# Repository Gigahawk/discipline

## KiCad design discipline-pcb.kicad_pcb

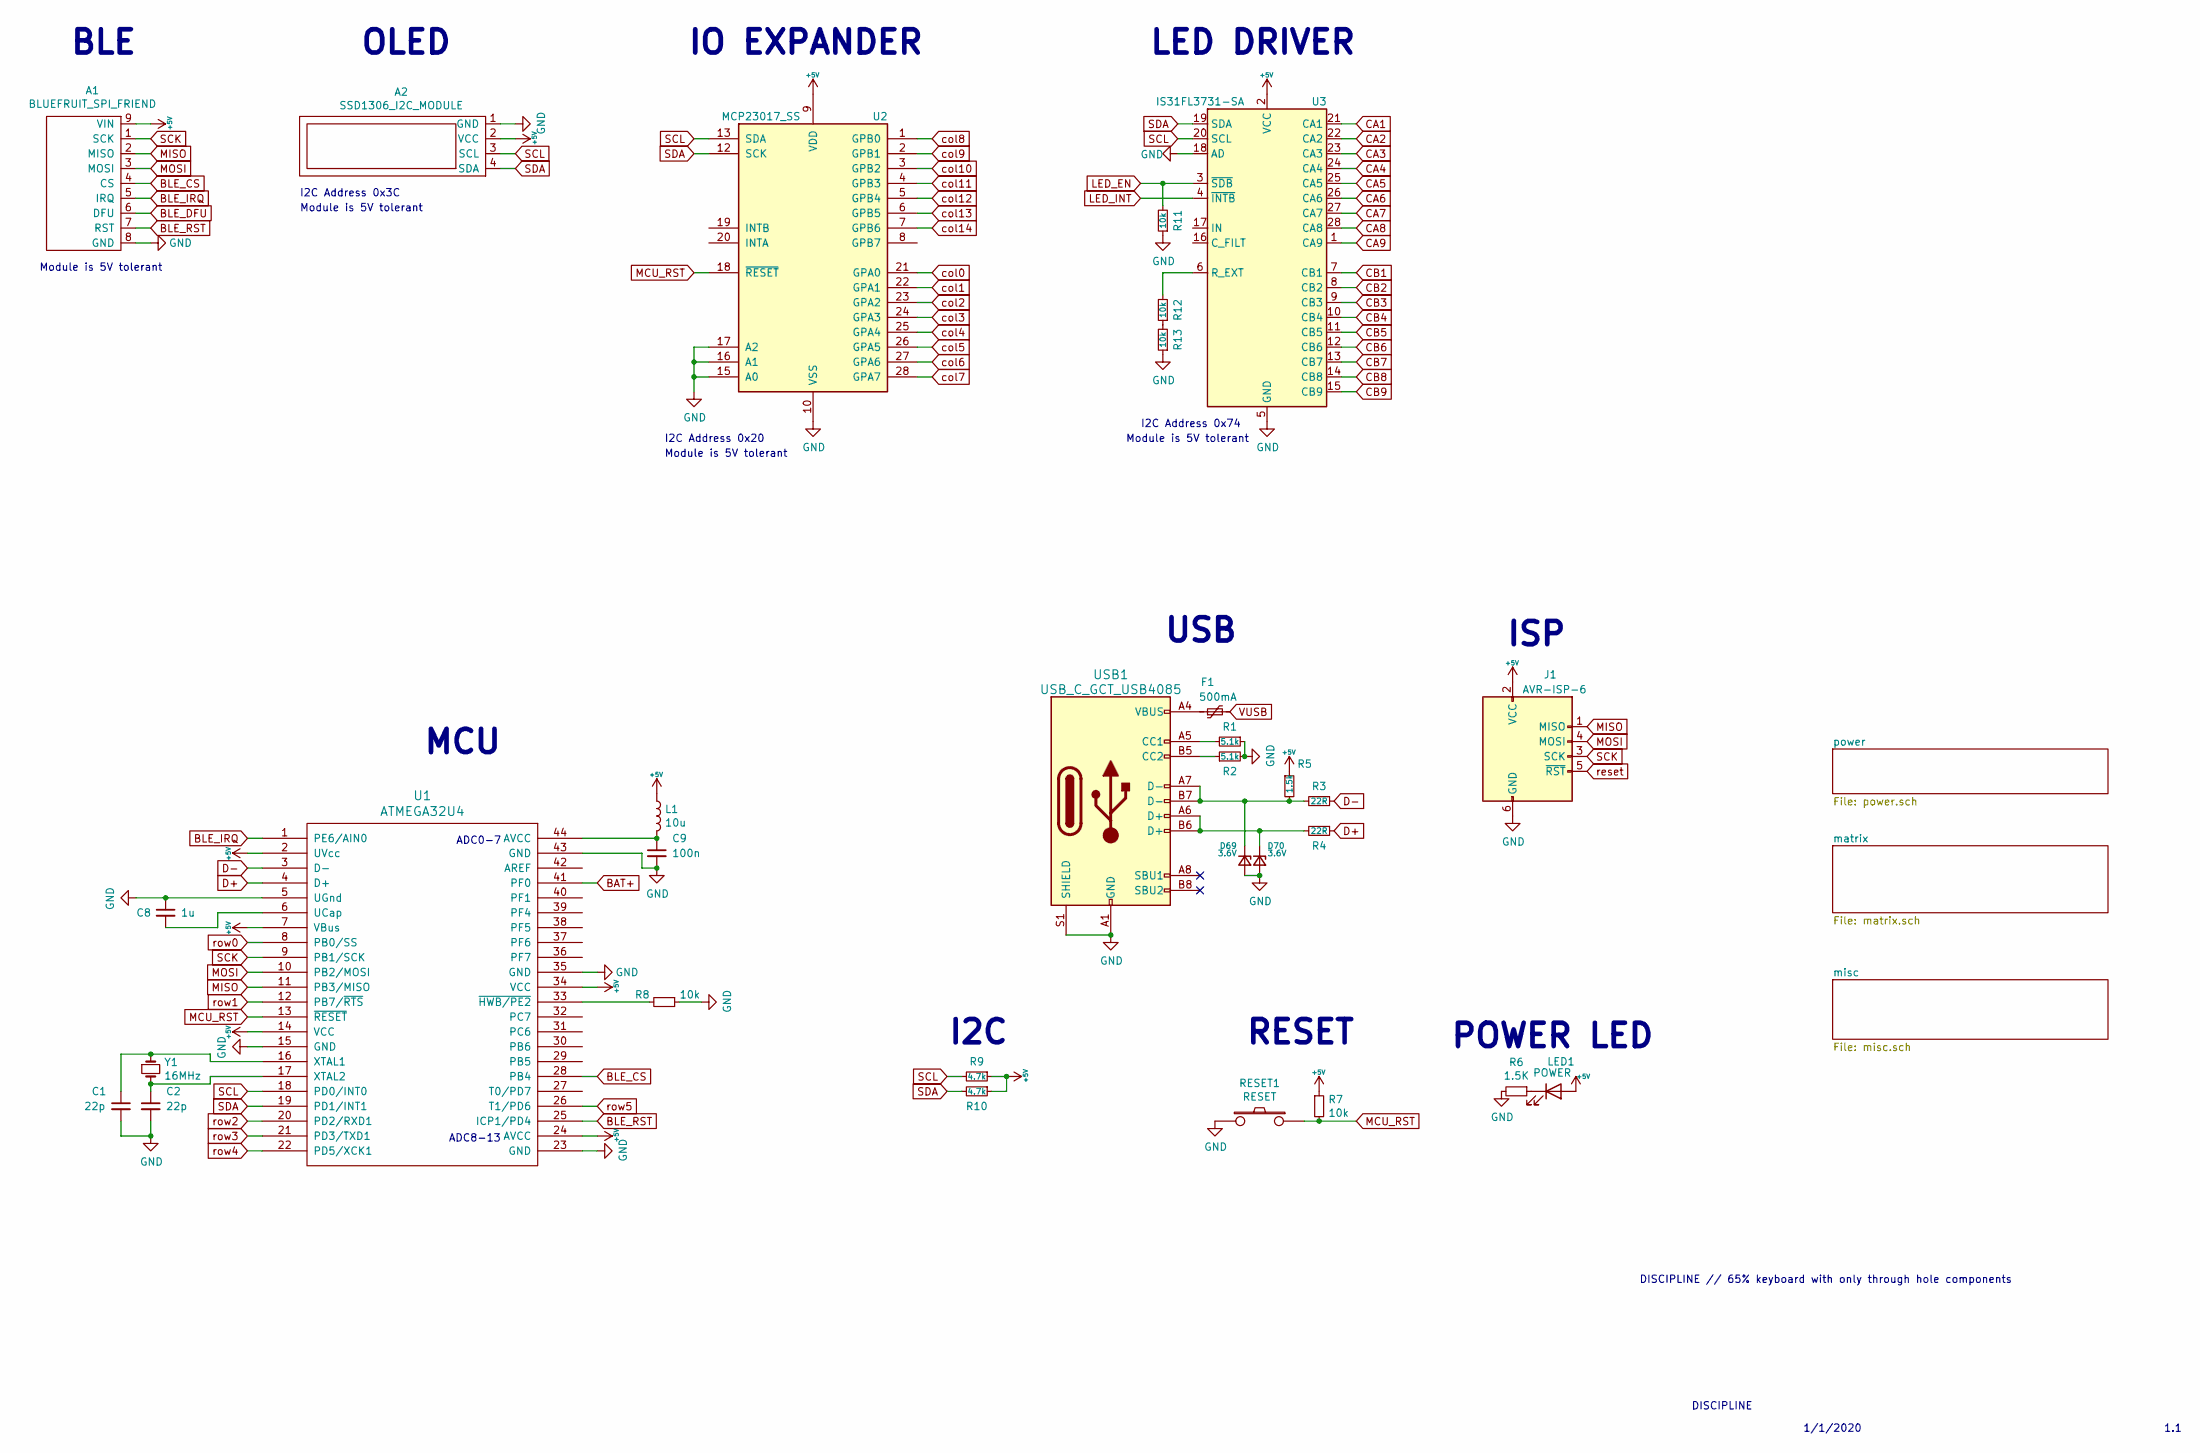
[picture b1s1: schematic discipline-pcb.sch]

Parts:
A1: BLUEFRUIT_SPI_FRIEND
A2: SSD1306_I2C_MODULE; SSD1306_MODULE_128x32
C1, C2: 22p; C_Disc_D3.0mm_W1.6mm_P2.50mm
C8: 1u; C_Disc_D3.0mm_W1.6mm_P2.50mm
C9: 100n; C_Disc_D3.0mm_W1.6mm_P2.50mm
D69, D70: 3.6V; D_SOD123_axial
F1: 500mA; polyfuse_5.1mm
J1: AVR-ISP-6; AVR_ICSP_3x2
L1: 10u
LED1: POWER; LED_D3.0mm
R1, R2: 5.1k; R_Axial_DIN0204_L3.6mm_D1.6mm_P5.08mm_Horizontal
R3, R4: 22R; R_Axial_DIN0204_L3.6mm_D1.6mm_P5.08mm_Horizontal
R5: 1.5k; R_Axial_DIN0204_L3.6mm_D1.6mm_P5.08mm_Horizontal
R6: 1.5K; R_Axial_DIN0204_L3.6mm_D1.6mm_P5.08mm_Horizontal
R7, R8, R11, R12, R13: 10k; R_Axial_DIN0204_L3.6mm_D1.6mm_P5.08mm_Horizontal
R9, R10: 4.7k; R_Axial_DIN0204_L3.6mm_D1.6mm_P5.08mm_Horizontal
RESET1: RESET; SW_PUSH_6mm
U1: ATMEGA32U4; TQFP-44_10x10mm_P0.8mm
U2: MCP23017_SS; SSOP-28_5.3x10.2mm_P0.65mm
U3: IS31FL3731-SA; SSOP-28_5.3x10.2mm_P0.65mm
USB1: USB_C_GCT_USB4085
Y1: 16MHz; Crystal_HC49-4H_Vertical

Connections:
+5V: A1.9 (VIN), A2.2 (VCC), J1.2 (VCC), L1.1, LED1.2 (A), R5.1, R7.1, R9.1, R10.1, U1.2 (UVcc), U1.7 (VBus), U1.14 (VCC), U1.24 (AVCC), U1.34 (VCC), U2.9 (VDD), U3.2 (VCC); also elsewhere on the board
BAT+: U1.41 (PF0); also elsewhere on the board
BLE_CS: A1.4 (CS), U1.28 (PB4)
BLE_DFU: A1.6 (DFU)
BLE_IRQ: A1.5 (IRQ), U1.1 (PE6/AIN0)
BLE_RST: A1.7 (RST), U1.25 (ICP1/PD4)
CA1: U3.21 (CA1); also elsewhere on the board
CA2: U3.22 (CA2); also elsewhere on the board
CA3: U3.23 (CA3); also elsewhere on the board
CA4: U3.24 (CA4); also elsewhere on the board
CA5: U3.25 (CA5); also elsewhere on the board
CA6: U3.26 (CA6); also elsewhere on the board
CA7: U3.27 (CA7); also elsewhere on the board
CA8: U3.28 (CA8); also elsewhere on the board
CA9: U3.1 (CA9); also elsewhere on the board
CB1: U3.7 (CB1); also elsewhere on the board
CB2: U3.8 (CB2); also elsewhere on the board
CB3: U3.9 (CB3); also elsewhere on the board
CB4: U3.10 (CB4); also elsewhere on the board
CB5: U3.11 (CB5); also elsewhere on the board
CB6: U3.12 (CB6); also elsewhere on the board
CB7: U3.13 (CB7); also elsewhere on the board
CB8: U3.14 (CB8); also elsewhere on the board
CB9: U3.15 (CB9)
D+: R4.1, U1.4 (D+)
D-: R3.1, U1.3 (D-)
GND: A1.8 (GND), A2.1 (GND), C1.2, C2.2, C8.1, C9.2, D69.2 (A), D70.2 (A), J1.6 (GND), R1.1, R2.2, R6.2, R8.1, R11.1, R13.1, RESET1.2, U1.5 (UGnd), U1.15 (GND), U1.23 (GND), U1.35 (GND), U1.43 (GND), U2.10 (VSS), U2.15 (A0), U2.16 (A1), U2.17 (A2), U3.5 (GND), U3.18 (AD), USB1.A1 (GND), USB1.A12 (GND), USB1.B1 (GND), USB1.B12 (GND), USB1.S1 (SHIELD); also elsewhere on the board
LED_EN: R11.2, U3.3 (~SDB)
LED_INT: U3.4 (~INTB)
MCU_RST: R7.2, RESET1.1, U1.13 (~RESET), U2.18 (~RESET~)
MISO: A1.2 (MISO), J1.1 (MISO), U1.11 (PB3/MISO)
MOSI: A1.3 (MOSI), J1.4 (MOSI), U1.10 (PB2/MOSI)
unnamed: C1.1, U1.16 (XTAL1), Y1.1
unnamed: C2.1, U1.17 (XTAL2), Y1.2
unnamed: C8.2, U1.6 (UCap)
unnamed: C9.1, L1.2, U1.44 (AVCC)
unnamed: D69.1 (K), R3.2, R5.2, USB1.A7 (D-), USB1.B7 (D-)
unnamed: D70.1 (K), R4.2, USB1.A6 (D+), USB1.B6 (D+)
unnamed: F1.1, USB1.A4 (VBUS), USB1.A9 (VBUS), USB1.B4 (VBUS), USB1.B9 (VBUS)
unnamed: LED1.1 (K), R6.1
unnamed: R1.2, USB1.A5 (CC1)
unnamed: R2.1, USB1.B5 (CC2)
unnamed: R8.2, U1.33 (~HWB/PE2)
unnamed: R12.1, R13.2
unnamed: R12.2, U3.6 (R_EXT)
SCK: A1.1 (SCK), J1.3 (SCK), U1.9 (PB1/SCK)
SCL: A2.3 (SCL), R9.2, U1.18 (PD0/INT0), U2.13 (SDA), U3.20 (SCL)
SDA: A2.4 (SDA), R10.2, U1.19 (PD1/INT1), U2.12 (SCK), U3.19 (SDA)
VUSB: F1.2; also elsewhere on the board
col0: U2.21 (GPA0); also elsewhere on the board
col1: U2.22 (GPA1); also elsewhere on the board
col2: U2.23 (GPA2); also elsewhere on the board
col3: U2.24 (GPA3); also elsewhere on the board
col4: U2.25 (GPA4); also elsewhere on the board
col5: U2.26 (GPA5); also elsewhere on the board
col6: U2.27 (GPA6); also elsewhere on the board
col7: U2.28 (GPA7); also elsewhere on the board
col8: U2.1 (GPB0); also elsewhere on the board
col9: U2.2 (GPB1); also elsewhere on the board
col10: U2.3 (GPB2); also elsewhere on the board
col11: U2.4 (GPB3); also elsewhere on the board
col12: U2.5 (GPB4); also elsewhere on the board
col13: U2.6 (GPB5); also elsewhere on the board
col14: U2.7 (GPB6); also elsewhere on the board
reset: J1.5 (~RST)

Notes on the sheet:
DISCIPLINE // 65% keyboard with only through hole components
1/1/2020
DISCIPLINE
1.1
MCU
USB
ISP
RESET
POWER LED
BLE
OLED
Module is 5V tolerant
Module is 5V tolerant
I2C Address 0x3C
ADC0-7
ADC8-13
IO EXPANDER
I2C Address 0x20
LED DRIVER
I2C Address 0x74
I2C

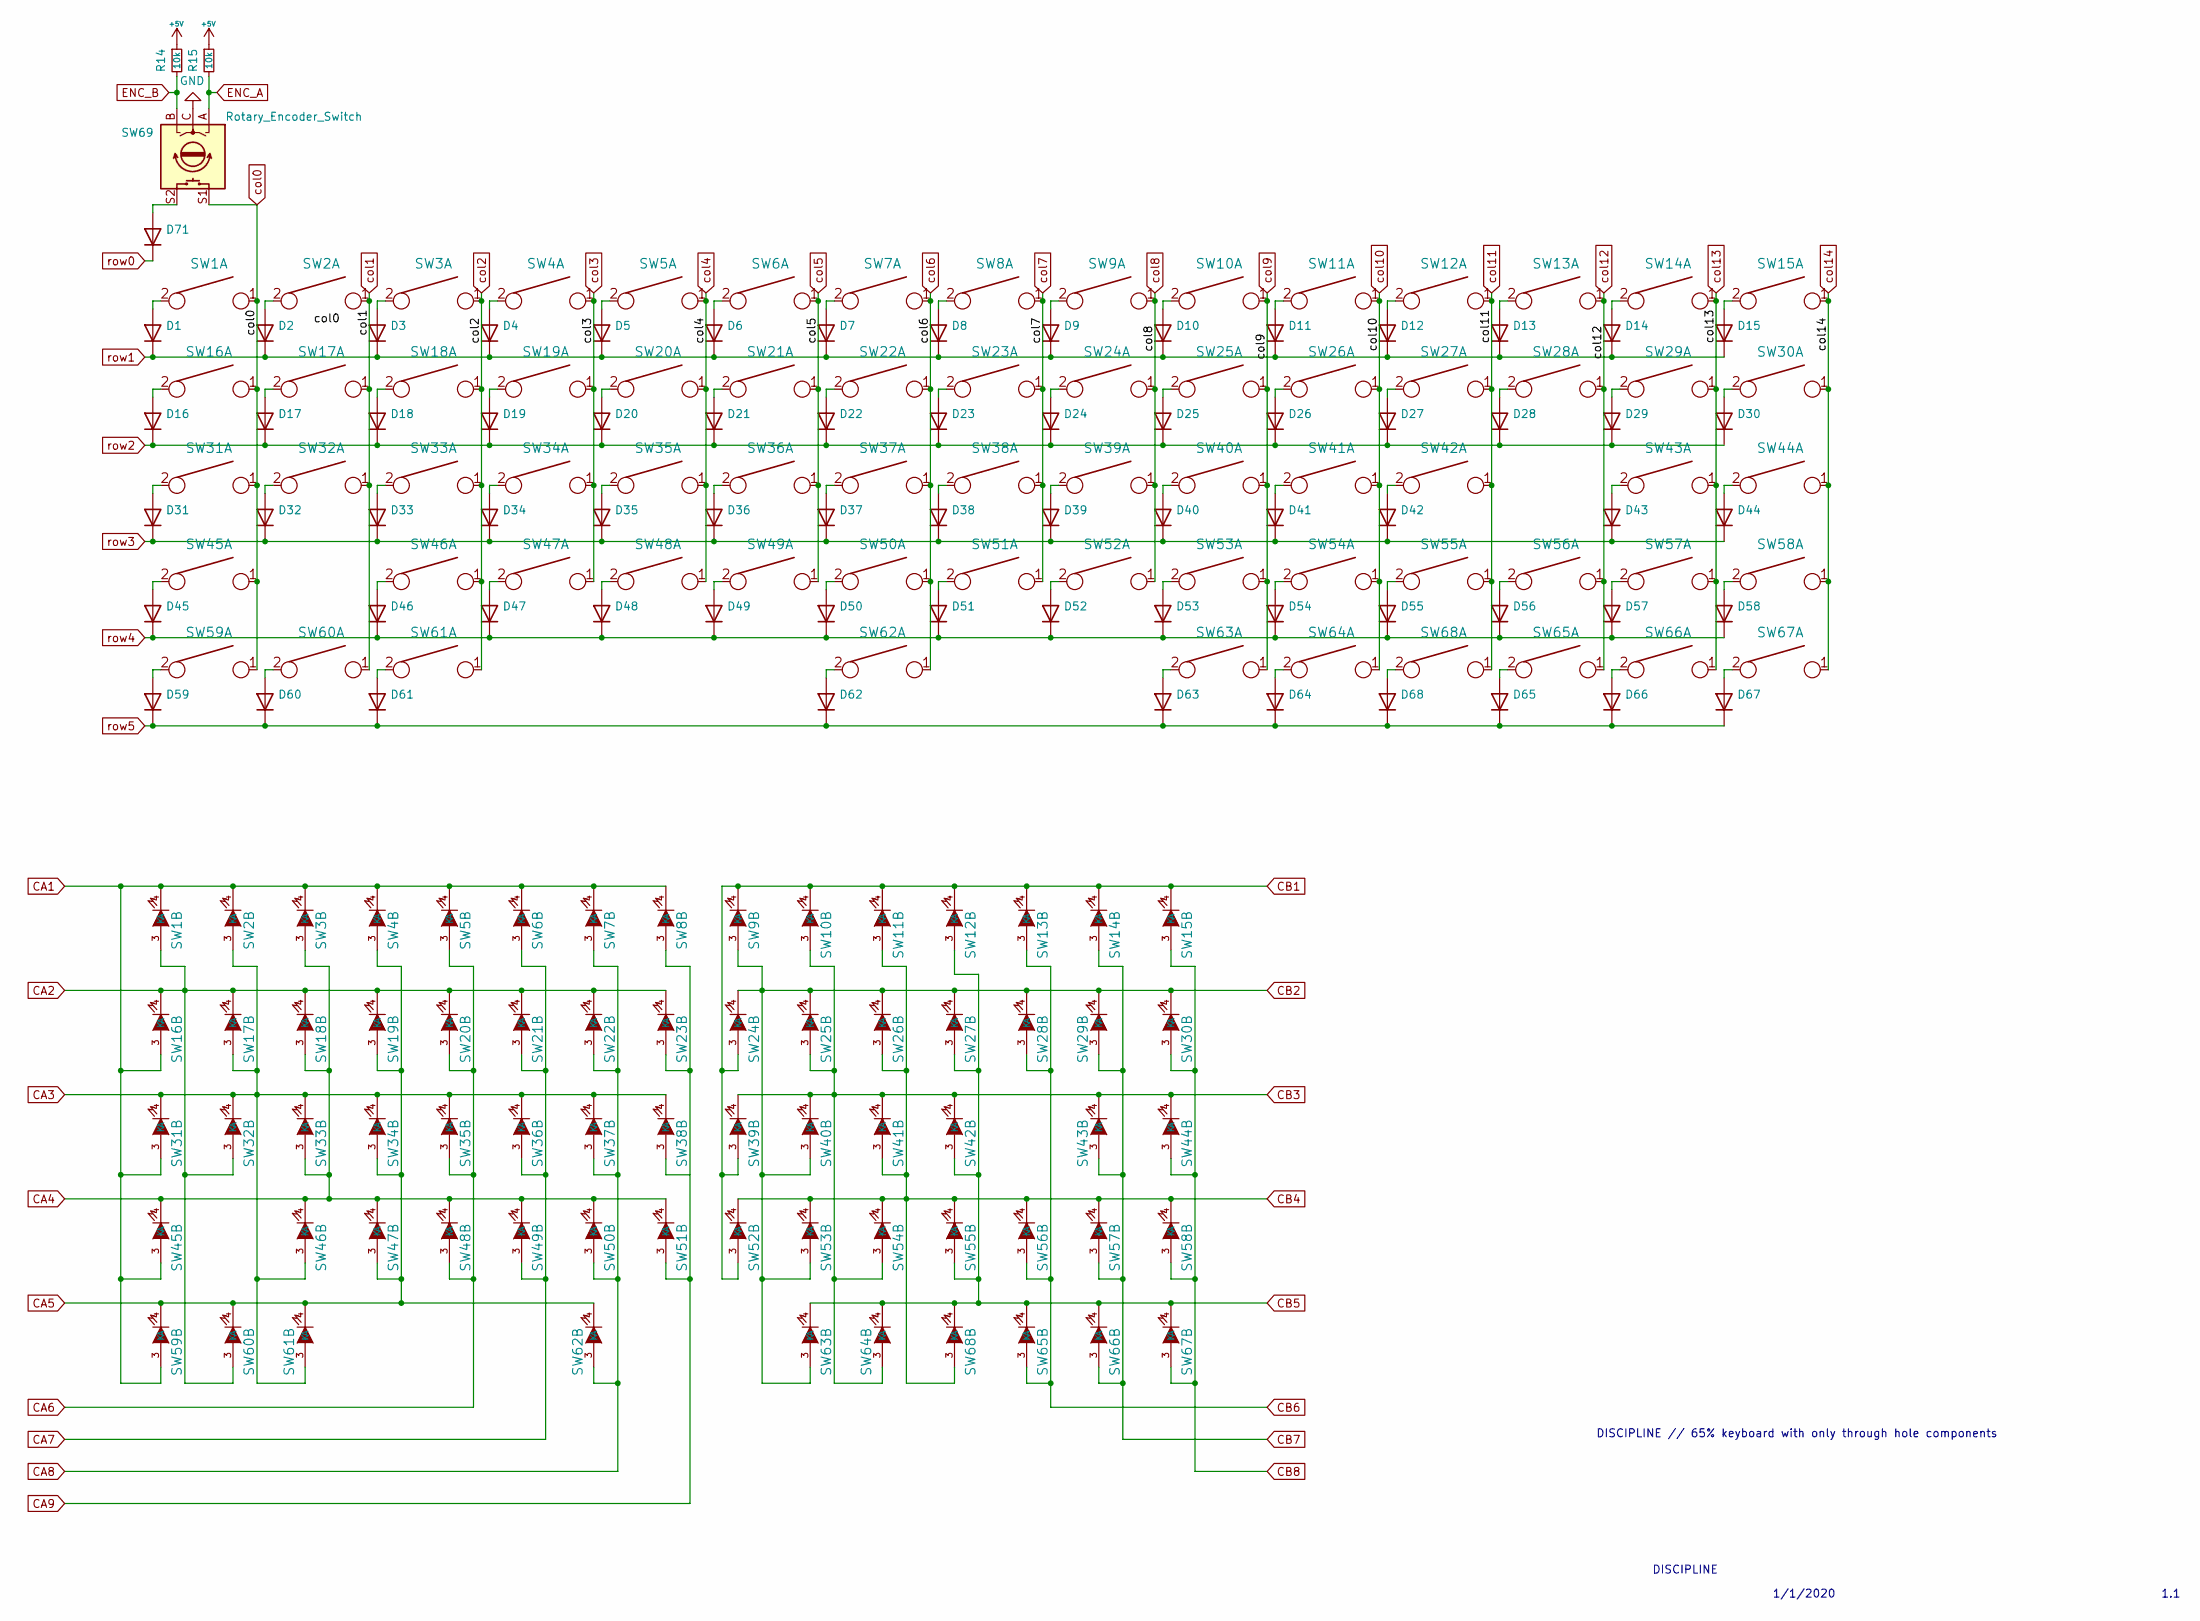
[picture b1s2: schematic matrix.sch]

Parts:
D1, D2, D3, D4, D5, D6, D7, D8, D9, D10, D11, D12, D13, D14, D15, D16, D17, D18, D19, D20, D21, D22, D23, D24, D25, D26, D27, D28, D29, D30, D31, D32, D33, D34, D35, D36, D37, D38, D39, D40, D41, D42, D43, D44, D45, D46, D47, D48, D49, D50, D51, D52, D53, D54, D55, D56, D57, D58, D59, D60, D61, D62, D63, D64, D65, D66, D67, D68, D71: D_SOD123_axial
R14, R15: 10k; R_Axial_DIN0204_L3.6mm_D1.6mm_P5.08mm_Horizontal
SW1, SW2, SW3, SW4, SW5, SW6, SW7, SW8, SW9, SW10, SW11, SW12, SW13, SW15, SW17, SW18, SW19, SW20, SW21, SW22, SW23, SW24, SW25, SW26, SW27, SW28, SW30, SW32, SW33, SW34, SW35, SW36, SW37, SW38, SW39, SW40, SW41, SW42, SW44, SW46, SW47, SW48, SW49, SW50, SW51, SW52, SW53, SW54, SW55, SW57, SW58, SW63, SW64, SW65, SW66, SW67, SW68: KEYSW; MX-1U
SW14: KEYSW; MX-2U
SW16, SW29: KEYSW; MX-1.5U
SW31, SW56: KEYSW; MX-1.75U
SW43, SW45: KEYSW; MX-2.25U
SW59, SW60, SW61: KEYSW; MX-1.25U
SW62: KEYSW; MX-6.25U-ReversedStabilizers
SW69: Rotary_Encoder_Switch; 482016514001

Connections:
CA1: SW1.4 (K), SW2.4 (K), SW3.4 (K), SW4.4 (K), SW5.4 (K), SW6.4 (K), SW7.4 (K), SW8.4 (K), SW16.3 (A), SW31.3 (A), SW45.3 (A), SW59.3 (A); also elsewhere on the board
CA2: SW1.3 (A), SW16.4 (K), SW17.4 (K), SW18.4 (K), SW19.4 (K), SW20.4 (K), SW21.4 (K), SW22.4 (K), SW23.4 (K), SW32.3 (A), SW60.3 (A); also elsewhere on the board
CA3: SW2.3 (A), SW17.3 (A), SW31.4 (K), SW32.4 (K), SW33.4 (K), SW34.4 (K), SW35.4 (K), SW36.4 (K), SW37.4 (K), SW38.4 (K), SW46.3 (A), SW61.3 (A); also elsewhere on the board
CA4: SW3.3 (A), SW18.3 (A), SW33.3 (A), SW45.4 (K), SW46.4 (K), SW47.4 (K), SW48.4 (K), SW49.4 (K), SW50.4 (K), SW51.4 (K); also elsewhere on the board
CA5: SW4.3 (A), SW19.3 (A), SW34.3 (A), SW47.3 (A), SW59.4 (K), SW60.4 (K), SW61.4 (K), SW62.4 (K); also elsewhere on the board
CA6: SW5.3 (A), SW20.3 (A), SW35.3 (A), SW48.3 (A); also elsewhere on the board
CA7: SW6.3 (A), SW21.3 (A), SW36.3 (A), SW49.3 (A); also elsewhere on the board
CA8: SW7.3 (A), SW22.3 (A), SW37.3 (A), SW50.3 (A), SW62.3 (A); also elsewhere on the board
CA9: SW8.3 (A), SW23.3 (A), SW51.3 (A); also elsewhere on the board
CB1: SW9.4 (K), SW10.4 (K), SW11.4 (K), SW12.4 (K), SW13.4 (K), SW14.4 (K), SW15.4 (K), SW24.3 (A), SW39.3 (A), SW52.3 (A); also elsewhere on the board
CB2: SW9.3 (A), SW24.4 (K), SW25.4 (K), SW26.4 (K), SW27.4 (K), SW28.4 (K), SW29.4 (K), SW30.4 (K), SW40.3 (A), SW53.3 (A), SW63.3 (A); also elsewhere on the board
CB3: SW10.3 (A), SW25.3 (A), SW39.4 (K), SW40.4 (K), SW41.4 (K), SW42.4 (K), SW43.4 (K), SW44.4 (K), SW54.3 (A), SW64.3 (A); also elsewhere on the board
CB4: SW11.3 (A), SW26.3 (A), SW41.3 (A), SW52.4 (K), SW53.4 (K), SW54.4 (K), SW55.4 (K), SW56.4 (K), SW57.4 (K), SW58.4 (K), SW68.3 (A); also elsewhere on the board
CB5: SW12.3 (A), SW27.3 (A), SW42.3 (A), SW55.3 (A), SW63.4 (K), SW64.4 (K), SW65.4 (K), SW66.4 (K), SW67.4 (K), SW68.4 (K); also elsewhere on the board
CB6: SW13.3 (A), SW28.3 (A), SW56.3 (A), SW65.3 (A); also elsewhere on the board
CB7: SW14.3 (A), SW29.3 (A), SW43.3 (A), SW57.3 (A), SW66.3 (A); also elsewhere on the board
CB8: SW15.3 (A), SW30.3 (A), SW44.3 (A), SW58.3 (A), SW67.3 (A); also elsewhere on the board
unnamed: D1.2 (A), SW1.2
unnamed: D2.2 (A), SW2.2
unnamed: D3.2 (A), SW3.2
unnamed: D4.2 (A), SW4.2
unnamed: D5.2 (A), SW5.2
unnamed: D6.2 (A), SW6.2
unnamed: D7.2 (A), SW7.2
unnamed: D8.2 (A), SW8.2
unnamed: D9.2 (A), SW9.2
unnamed: D10.2 (A), SW10.2
unnamed: D11.2 (A), SW11.2
unnamed: D12.2 (A), SW12.2
unnamed: D13.2 (A), SW13.2
unnamed: D14.2 (A), SW14.2
unnamed: D15.2 (A), SW15.2
unnamed: D16.2 (A), SW16.2
unnamed: D17.2 (A), SW17.2
unnamed: D18.2 (A), SW18.2
unnamed: D19.2 (A), SW19.2
unnamed: D20.2 (A), SW20.2
unnamed: D21.2 (A), SW21.2
unnamed: D22.2 (A), SW22.2
unnamed: D23.2 (A), SW23.2
unnamed: D24.2 (A), SW24.2
unnamed: D25.2 (A), SW25.2
unnamed: D26.2 (A), SW26.2
unnamed: D27.2 (A), SW27.2
unnamed: D28.2 (A), SW28.2
unnamed: D29.2 (A), SW29.2
unnamed: D30.2 (A), SW30.2
unnamed: D31.2 (A), SW31.2
unnamed: D32.2 (A), SW32.2
unnamed: D33.2 (A), SW33.2
unnamed: D34.2 (A), SW34.2
unnamed: D35.2 (A), SW35.2
unnamed: D36.2 (A), SW36.2
unnamed: D37.2 (A), SW37.2
unnamed: D38.2 (A), SW38.2
unnamed: D39.2 (A), SW39.2
unnamed: D40.2 (A), SW40.2
unnamed: D41.2 (A), SW41.2
unnamed: D42.2 (A), SW42.2
unnamed: D43.2 (A), SW43.2
unnamed: D44.2 (A), SW44.2
unnamed: D45.2 (A), SW45.2
unnamed: D46.2 (A), SW46.2
unnamed: D47.2 (A), SW47.2
unnamed: D48.2 (A), SW48.2
unnamed: D49.2 (A), SW49.2
unnamed: D50.2 (A), SW50.2
unnamed: D51.2 (A), SW51.2
unnamed: D52.2 (A), SW52.2
unnamed: D53.2 (A), SW53.2
unnamed: D54.2 (A), SW54.2
unnamed: D55.2 (A), SW55.2
unnamed: D56.2 (A), SW56.2
unnamed: D57.2 (A), SW57.2
unnamed: D58.2 (A), SW58.2
unnamed: D59.2 (A), SW59.2
unnamed: D60.2 (A), SW60.2
unnamed: D61.2 (A), SW61.2
unnamed: D62.2 (A), SW62.2
unnamed: D63.2 (A), SW63.2
unnamed: D64.2 (A), SW64.2
unnamed: D65.2 (A), SW65.2
unnamed: D66.2 (A), SW66.2
unnamed: D67.2 (A), SW67.2
unnamed: D68.2 (A), SW68.2
unnamed: D71.2 (A), SW69.S2
unnamed: R14.1, R15.1
unnamed: R14.2, SW69.B
unnamed: R15.2, SW69.A
col0: SW1.1, SW16.1, SW31.1, SW45.1, SW59.1, SW69.S1; also elsewhere on the board
col1: SW2.1, SW17.1, SW32.1, SW60.1; also elsewhere on the board
col2: SW3.1, SW18.1, SW33.1, SW46.1, SW61.1; also elsewhere on the board
col3: SW4.1, SW19.1, SW34.1, SW47.1; also elsewhere on the board
col4: SW5.1, SW20.1, SW35.1, SW48.1; also elsewhere on the board
col5: SW6.1, SW21.1, SW36.1, SW49.1; also elsewhere on the board
col6: SW7.1, SW22.1, SW37.1, SW50.1, SW62.1; also elsewhere on the board
col7: SW8.1, SW23.1, SW38.1, SW51.1; also elsewhere on the board
col8: SW9.1, SW24.1, SW39.1, SW52.1; also elsewhere on the board
col9: SW10.1, SW25.1, SW40.1, SW53.1, SW63.1; also elsewhere on the board
col10: SW11.1, SW26.1, SW41.1, SW54.1, SW64.1; also elsewhere on the board
col11: SW12.1, SW27.1, SW42.1, SW55.1, SW68.1; also elsewhere on the board
col12: SW13.1, SW28.1, SW56.1, SW65.1; also elsewhere on the board
col13: SW14.1, SW29.1, SW43.1, SW57.1, SW66.1; also elsewhere on the board
col14: SW15.1, SW30.1, SW44.1, SW58.1, SW67.1; also elsewhere on the board
row0: D1.1 (K), D2.1 (K), D3.1 (K), D4.1 (K), D5.1 (K), D6.1 (K), D7.1 (K), D8.1 (K), D9.1 (K), D10.1 (K), D11.1 (K), D12.1 (K), D13.1 (K), D14.1 (K), D15.1 (K)
row1: D16.1 (K), D17.1 (K), D18.1 (K), D19.1 (K), D20.1 (K), D21.1 (K), D22.1 (K), D23.1 (K), D24.1 (K), D25.1 (K), D26.1 (K), D27.1 (K), D28.1 (K), D29.1 (K), D30.1 (K)
row2: D31.1 (K), D32.1 (K), D33.1 (K), D34.1 (K), D35.1 (K), D36.1 (K), D37.1 (K), D38.1 (K), D39.1 (K), D40.1 (K), D41.1 (K), D42.1 (K), D43.1 (K), D44.1 (K)
row3: D45.1 (K), D46.1 (K), D47.1 (K), D48.1 (K), D49.1 (K), D50.1 (K), D51.1 (K), D52.1 (K), D53.1 (K), D54.1 (K), D55.1 (K), D56.1 (K), D57.1 (K), D58.1 (K)
row4: D59.1 (K), D60.1 (K), D61.1 (K), D62.1 (K), D63.1 (K), D64.1 (K), D65.1 (K), D66.1 (K), D67.1 (K), D68.1 (K)

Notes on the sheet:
DISCIPLINE // 65% keyboard with only through hole components
1/1/2020
DISCIPLINE
1.1

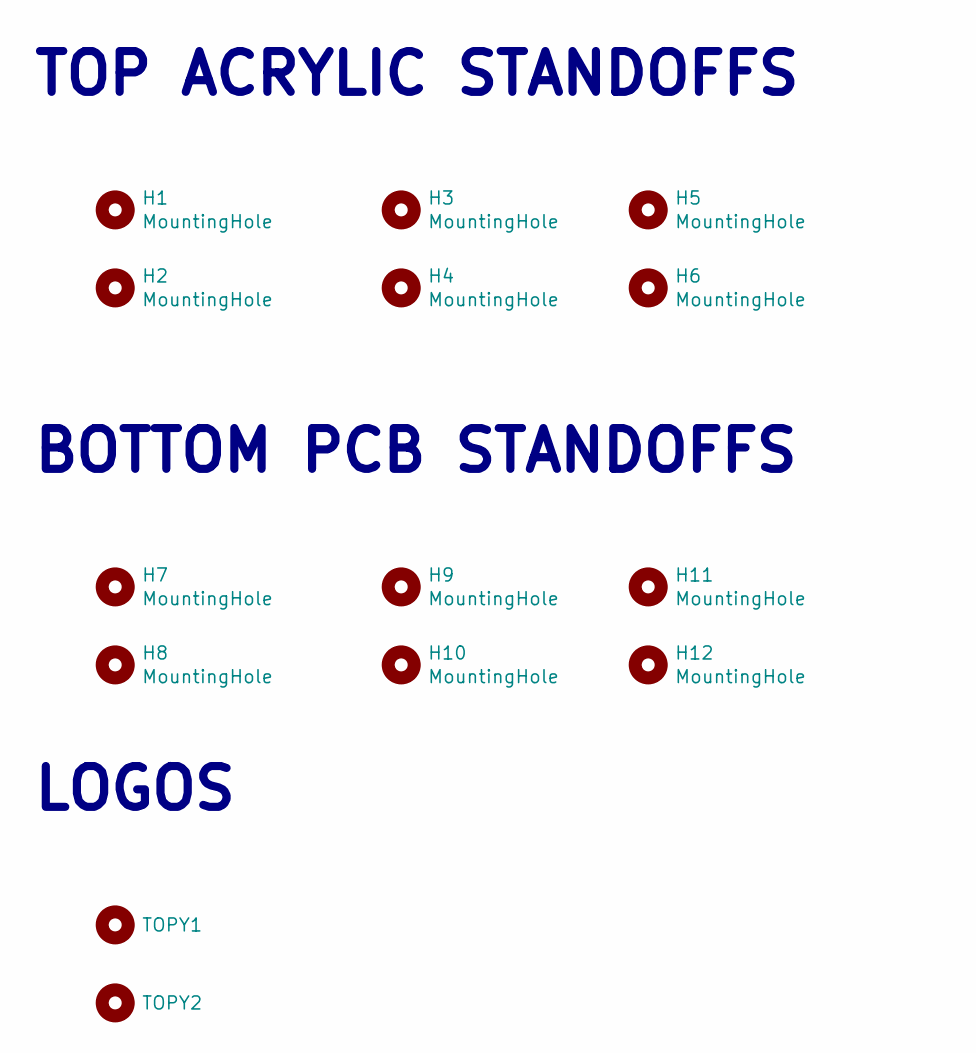
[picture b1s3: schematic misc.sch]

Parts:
H1, H2, H3, H4, H5, H6, H7, H8, H9, H10, H11, H12: MountingHole; MountingHole_2.2mm_M2_Pad
TOPY1, TOPY2: MountingHole; TOPY 4MM MASK

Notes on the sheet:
TOP ACRYLIC STANDOFFS
BOTTOM PCB STANDOFFS
LOGOS

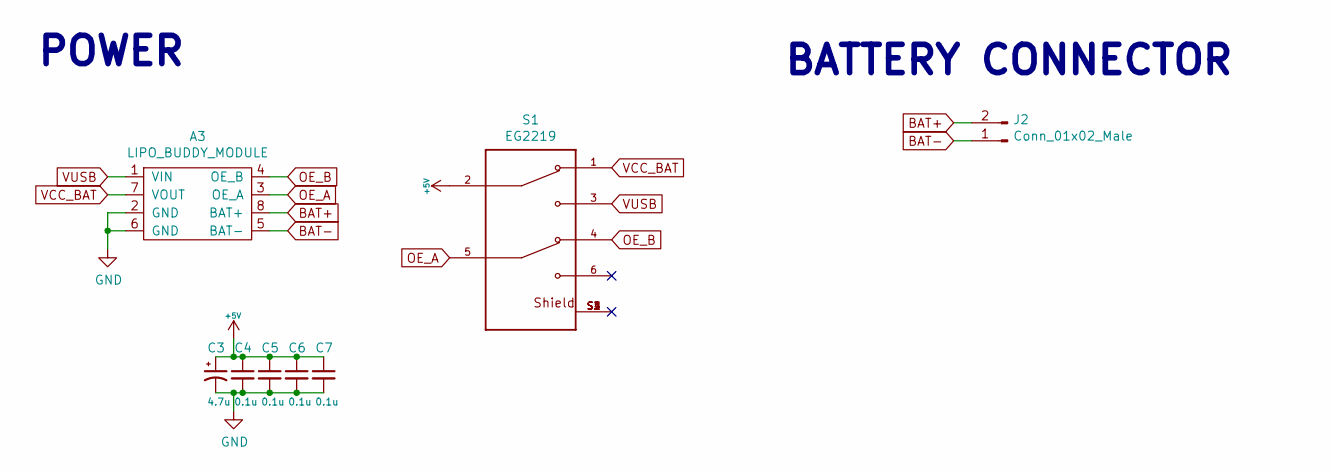
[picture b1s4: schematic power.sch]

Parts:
A3: LIPO_BUDDY_MODULE
C3: 4.7u; CP_Radial_D4.0mm_P1.50mm
C4, C5, C6, C7: 0.1u; C_Disc_D4.3mm_W1.9mm_P5.00mm
J2: Conn_01x02_Male; JST_PH_S2B-PH-K_1x02_P2.00mm_Horizontal
S1: EG2219; SW_EG2219

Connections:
+5V: C3.1, C4.1, C5.1, C6.1, C7.1, S1.2 (COM_2); also elsewhere on the board
BAT+: A3.8 (BAT+), J2.2; also elsewhere on the board
BAT-: A3.5 (BAT-), J2.1
GND: A3.2 (GND), A3.6 (GND), C3.2, C4.2, C5.2, C6.2, C7.2; also elsewhere on the board
unnamed: S1.S1 (SHIELD), S1.S2 (SHIELD), S1.S3 (SHIELD), S1.S4 (SHIELD)
OE_A: A3.3 (OE_A), S1.5 (COM_5)
OE_B: A3.4 (OE_B), S1.4
VCC_BAT: A3.7 (VOUT), S1.1
VUSB: A3.1 (VIN), S1.3; also elsewhere on the board

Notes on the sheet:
POWER
BATTERY CONNECTOR

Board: 2 copper layers, 188 parts (69 on the bottom side), 139 nets, no tracks yet.

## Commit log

2020-08-02 Replace keyswitch footprint with MX_Alps_Hybrid
2020-08-02 Remove ISO layout, add led matrix to schematic
2020-08-02 Misc cleanup, delete tracks to prepare for bigger changes
2020-08-02 Move diodes to key area
2020-08-06 Add power, oled, ble modules
2020-08-09 Add rotary encoder
